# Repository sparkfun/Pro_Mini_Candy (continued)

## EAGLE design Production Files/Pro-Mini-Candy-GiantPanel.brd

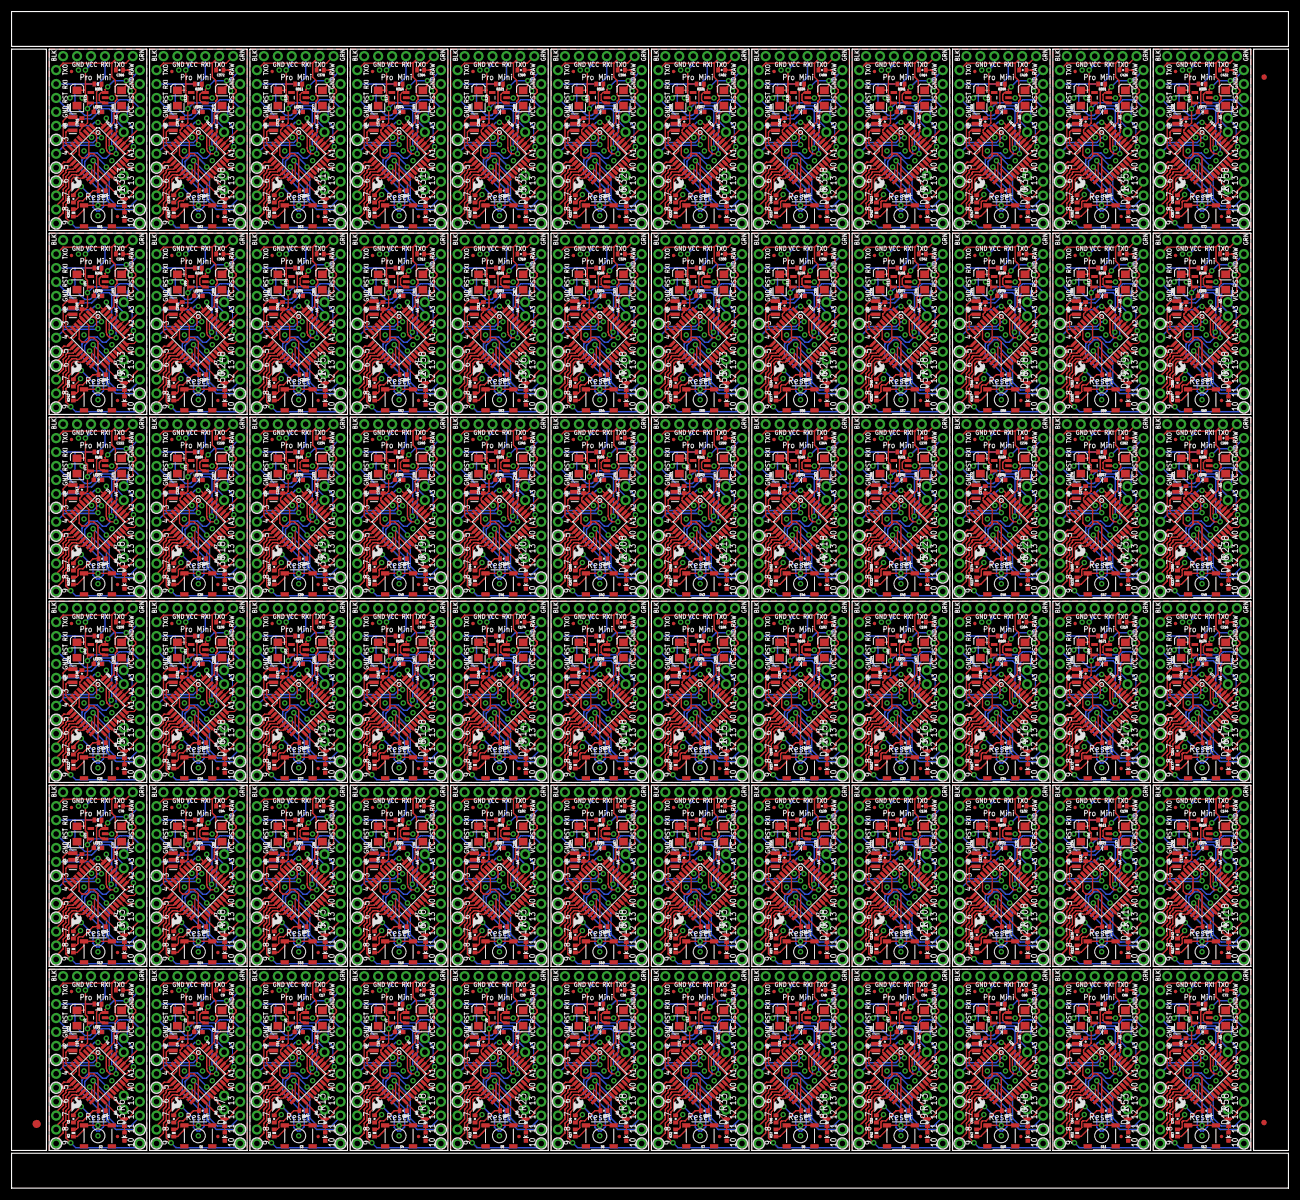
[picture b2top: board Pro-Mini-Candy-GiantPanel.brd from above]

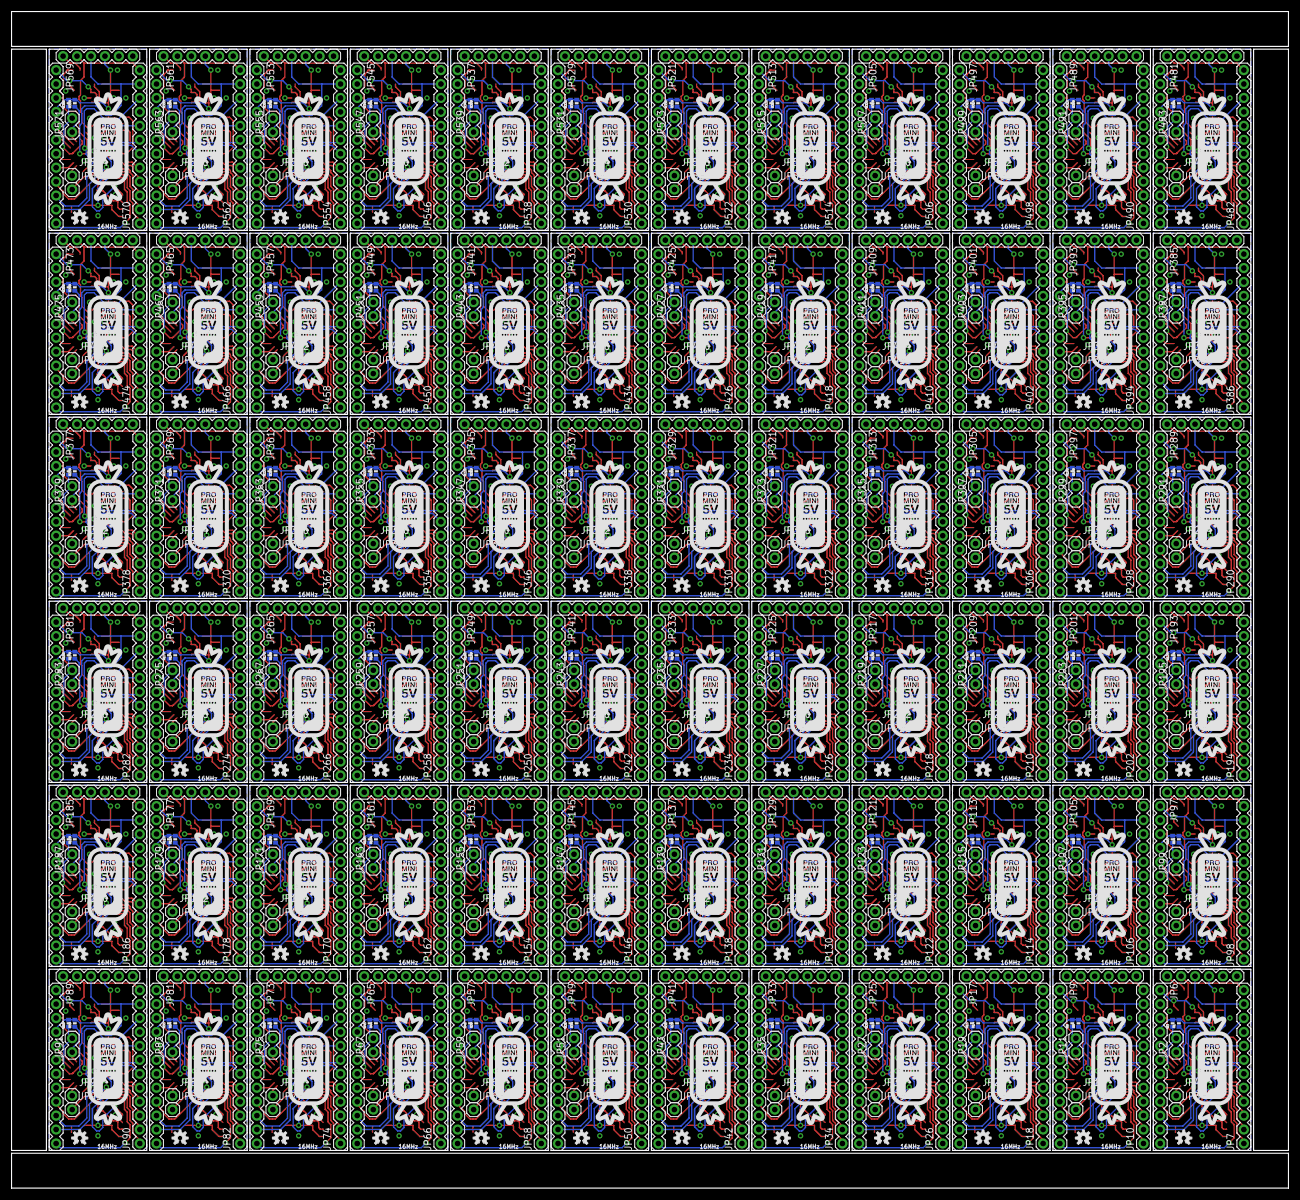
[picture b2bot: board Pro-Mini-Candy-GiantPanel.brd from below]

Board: 2 copper layers, 232.7 x 214.4 mm, 2019 parts (720 on the bottom side), 2304 nets.

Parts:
C1, C2, C3, C4, C6, C7, C9, C10, C11, C14, C15, C17, C18, C21, C22, C24, C25, C27, C28, C30, C31, C33, C34, C36, C37, C39, C40, C42, C43, C45, C46, C48, C49, C51, C52, C54, C55, C57, C58, C60, C61, C63, C64, C66, C67, C69, C70, C72, C73, C75, C76, C78, C79, C81, C82, C84, C85, C87, C88, C90, C91, C93, C94, C96, C97, C99, C100, C102, C103, C105, C106, C108, C109, C111, C112, C114, C115, C117, C118, C120, C121, C123, C124, C126, C127, C129, C130, C132, C133, C135, C136, C138, C139, C141, C142, C144, C145, C147, C148, C150, C151, C153, C154, C156, C157, C159, C160, C162, C163, C165, C166, C168, C169, C171, C172, C174, C175, C177, C178, C180, C181, C183, C184, C186, C187, C189, C190, C192, C193, C195, C196, C198, C199, C201, C202, C204, C205, C207, C208, C210, C211, C213, C214, C216, C217, C219, C220, C222, C223, C225, C226, C228, C229, C231, C232, C234, C235, C237, C238, C240, C241, C243, C244, C246, C247, C249, C250, C252, C253, C255, C256, C258, C259, C261, C262, C264, C265, C267, C268, C270, C271, C273, C274, C276, C277, C279, C280, C282, C283, C285, C286, C288, C289, C291, C292, C294, C295, C297, C298, C300, C301, C303, C304, C306, C307, C309, C310, C312, C313, C315, C316, C318, C319, C321, C322, C324, C325, C327, C328, C330, C331, C333, C334, C336, C337, C339, C340, C342, C343, C345, C346, C348, C349, C351, C352, C354, C355, C357, C358, C360, C361, C363, C364, C366, C367, C369, C370, C372, C373, C375, C376, C378, C379, C381, C382, C384, C385, C387, C388, C390, C391, C393, C394, C396, C397, C399, C400, C402, C403, C405, C406, C408, C409, C411, C412, C414, C415, C417, C418, C420, C421, C423, C424, C426, C427, C429, C430, C432: 0.1uF; 0402-CAP
C5, C8, C12, C13, C16, C19, C20, C23, C26, C29, C32, C35, C38, C41, C44, C47, C50, C53, C56, C59, C62, C65, C68, C71, C74, C77, C80, C83, C86, C89, C92, C95, C98, C101, C104, C107, C110, C113, C116, C119, C122, C125, C128, C131, C134, C137, C140, C143, C146, C149, C152, C155, C158, C161, C164, C167, C170, C173, C176, C179, C182, C185, C188, C191, C194, C197, C200, C203, C206, C209, C212, C215, C218, C221, C224, C227, C230, C233, C236, C239, C242, C245, C248, C251, C254, C257, C260, C263, C266, C269, C272, C275, C278, C281, C284, C287, C290, C293, C296, C299, C302, C305, C308, C311, C314, C317, C320, C323, C326, C329, C332, C335, C338, C341, C344, C347, C350, C353, C356, C359, C362, C365, C368, C371, C374, C377, C380, C383, C386, C389, C392, C395, C398, C401, C404, C407, C410, C413, C416, C419, C422, C425, C428, C431: 10uF; EIA3216
D1, D2, D3, D4, D5, D6, D7, D8, D9, D10, D11, D12, D13, D14, D15, D16, D17, D18, D19, D20, D21, D22, D23, D24, D25, D26, D27, D28, D29, D30, D31, D32, D33, D34, D35, D36, D37, D38, D39, D40, D41, D42, D43, D44, D45, D46, D47, D48, D49, D50, D51, D52, D53, D54, D55, D56, D57, D58, D59, D60, D61, D62, D63, D64, D65, D66, D67, D68, D69, D70, D71, D72: Green; LED-0603
E$1: FIDUCIAL-1.5X3
E$4, E$5: FIDUCIAL-1X2
JP1, JP12, JP20, JP28, JP36, JP44, JP52, JP60, JP68, JP76, JP84, JP92, JP100, JP108, JP116, JP124, JP132, JP140, JP148, JP156, JP164, JP172, JP180, JP188, JP196, JP204, JP212, JP220, JP228, JP236, JP244, JP252, JP260, JP268, JP276, JP284, JP292, JP300, JP308, JP316, JP324, JP332, JP340, JP348, JP356, JP364, JP372, JP380, JP388, JP396, JP404, JP412, JP420, JP428, JP436, JP444, JP452, JP460, JP468, JP476, JP484, JP492, JP500, JP508, JP516, JP524, JP532, JP540, JP548, JP556, JP564, JP572: FTDI Basic; 1X06
JP2, JP11, JP19, JP27, JP35, JP43, JP51, JP59, JP67, JP75, JP83, JP91, JP99, JP107, JP115, JP123, JP131, JP139, JP147, JP155, JP163, JP171, JP179, JP187, JP195, JP203, JP211, JP219, JP227, JP235, JP243, JP251, JP259, JP267, JP275, JP283, JP291, JP299, JP307, JP315, JP323, JP331, JP339, JP347, JP355, JP363, JP371, JP379, JP387, JP395, JP403, JP411, JP419, JP427, JP435, JP443, JP451, JP459, JP467, JP475, JP483, JP491, JP499, JP507, JP515, JP523, JP531, JP539, JP547, JP555, JP563, JP571: 1X02
JP3, JP4, JP13, JP14, JP21, JP22, JP29, JP30, JP37, JP38, JP45, JP46, JP53, JP54, JP61, JP62, JP69, JP70, JP77, JP78, JP85, JP86, JP93, JP94, JP101, JP102, JP109, JP110, JP117, JP118, JP125, JP126, JP133, JP134, JP141, JP142, JP149, JP150, JP157, JP158, JP165, JP166, JP173, JP174, JP181, JP182, JP189, JP190, JP197, JP198, JP205, JP206, JP213, JP214, JP221, JP222, JP229, JP230, JP237, JP238, JP245, JP246, JP253, JP254, JP261, JP262, JP269, JP270, JP277, JP278, JP285, JP286, JP293, JP294, JP301, JP302, JP309, JP310, JP317, JP318, JP325, JP326, JP333, JP334, JP341, JP342, JP349, JP350, JP357, JP358, JP365, JP366, JP373, JP374, JP381, JP382, JP389, JP390, JP397, JP398, JP405, JP406, JP413, JP414, JP421, JP422, JP429, JP430, JP437, JP438, JP445, JP446, JP453, JP454, JP461, JP462, JP469, JP470, JP477, JP478, JP485, JP486, JP493, JP494, JP501, JP502, JP509, JP510, JP517, JP518, JP525, JP526, JP533, JP534, JP541, JP542, JP549, JP550, JP557, JP558, JP565, JP566, JP573, JP574: 1X01
JP5, JP8, JP15, JP16, JP23, JP24, JP31, JP32, JP39, JP40, JP47, JP48, JP55, JP56, JP63, JP64, JP71, JP72, JP79, JP80, JP87, JP88, JP95, JP96, JP103, JP104, JP111, JP112, JP119, JP120, JP127, JP128, JP135, JP136, JP143, JP144, JP151, JP152, JP159, JP160, JP167, JP168, JP175, JP176, JP183, JP184, JP191, JP192, JP199, JP200, JP207, JP208, JP215, JP216, JP223, JP224, JP231, JP232, JP239, JP240, JP247, JP248, JP255, JP256, JP263, JP264, JP271, JP272, JP279, JP280, JP287, JP288, JP295, JP296, JP303, JP304, JP311, JP312, JP319, JP320, JP327, JP328, JP335, JP336, JP343, JP344, JP351, JP352, JP359, JP360, JP367, JP368, JP375, JP376, JP383, JP384, JP391, JP392, JP399, JP400, JP407, JP408, JP415, JP416, JP423, JP424, JP431, JP432, JP439, JP440, JP447, JP448, JP455, JP456, JP463, JP464, JP471, JP472, JP479, JP480, JP487, JP488, JP495, JP496, JP503, JP504, JP511, JP512, JP519, JP520, JP527, JP528, JP535, JP536, JP543, JP544, JP551, JP552, JP559, JP560, JP567, JP568, JP575, JP576: FIDUCIALUFIDUCIAL; MICRO-FIDUCIAL
JP6, JP7, JP9, JP10, JP17, JP18, JP25, JP26, JP33, JP34, JP41, JP42, JP49, JP50, JP57, JP58, JP65, JP66, JP73, JP74, JP81, JP82, JP89, JP90, JP97, JP98, JP105, JP106, JP113, JP114, JP121, JP122, JP129, JP130, JP137, JP138, JP145, JP146, JP153, JP154, JP161, JP162, JP169, JP170, JP177, JP178, JP185, JP186, JP193, JP194, JP201, JP202, JP209, JP210, JP217, JP218, JP225, JP226, JP233, JP234, JP241, JP242, JP249, JP250, JP257, JP258, JP265, JP266, JP273, JP274, JP281, JP282, JP289, JP290, JP297, JP298, JP305, JP306, JP313, JP314, JP321, JP322, JP329, JP330, JP337, JP338, JP345, JP346, JP353, JP354, JP361, JP362, JP369, JP370, JP377, JP378, JP385, JP386, JP393, JP394, JP401, JP402, JP409, JP410, JP417, JP418, JP425, JP426, JP433, JP434, JP441, JP442, JP449, JP450, JP457, JP458, JP465, JP466, JP473, JP474, JP481, JP482, JP489, JP490, JP497, JP498, JP505, JP506, JP513, JP514, JP521, JP522, JP529, JP530, JP537, JP538, JP545, JP546, JP553, JP554, JP561, JP562, JP569, JP570: 1X12
LED1, LED2, LED3, LED4, LED5, LED6, LED7, LED8, LED9, LED10, LED11, LED12, LED13, LED14, LED15, LED16, LED17, LED18, LED19, LED20, LED21, LED22, LED23, LED24, LED25, LED26, LED27, LED28, LED29, LED30, LED31, LED32, LED33, LED34, LED35, LED36, LED37, LED38, LED39, LED40, LED41, LED42, LED43, LED44, LED45, LED46, LED47, LED48, LED49, LED50, LED51, LED52, LED53, LED54, LED55, LED56, LED57, LED58, LED59, LED60, LED61, LED62, LED63, LED64, LED65, LED66, LED67, LED68, LED69, LED70, LED71, LED72: Red; LED-0603
Q1, Q2, Q3, Q4, Q5, Q6, Q7, Q8, Q9, Q10, Q11, Q12, Q13, Q14, Q15, Q16, Q17, Q18, Q19, Q20, Q21, Q22, Q23, Q24, Q25, Q26, Q27, Q28, Q29, Q30, Q31, Q32, Q33, Q34, Q35, Q36, Q37, Q38, Q39, Q40, Q41, Q42, Q43, Q44, Q45, Q46, Q47, Q48, Q49, Q50, Q51, Q52, Q53, Q54, Q55, Q56, Q57, Q58, Q59, Q60, Q61, Q62, Q63, Q64, Q65, Q66, Q67, Q68, Q69, Q70, Q71, Q72: 8/16/20MHz; RESONATOR-SMD
R1, R3, R8, R9, R14, R15, R19, R20, R24, R25, R29, R30, R34, R35, R39, R40, R44, R45, R49, R50, R54, R55, R59, R60, R64, R65, R69, R70, R74, R75, R79, R80, R84, R85, R89, R90, R94, R95, R99, R100, R104, R105, R109, R110, R114, R115, R119, R120, R124, R125, R129, R130, R134, R135, R139, R140, R144, R145, R149, R150, R154, R155, R159, R160, R164, R165, R169, R170, R174, R175, R179, R180, R184, R185, R189, R190, R194, R195, R199, R200, R204, R205, R209, R210, R214, R215, R219, R220, R224, R225, R229, R230, R234, R235, R239, R240, R244, R245, R249, R250, R254, R255, R259, R260, R264, R265, R269, R270, R274, R275, R279, R280, R284, R285, R289, R290, R294, R295, R299, R300, R304, R305, R309, R310, R314, R315, R319, R320, R324, R325, R329, R330, R334, R335, R339, R340, R344, R345, R349, R350, R354, R355, R359, R360: 0402-RES
R2, R4, R5, R10, R11, R12, R16, R17, R21, R22, R26, R27, R31, R32, R36, R37, R41, R42, R46, R47, R51, R52, R56, R57, R61, R62, R66, R67, R71, R72, R76, R77, R81, R82, R86, R87, R91, R92, R96, R97, R101, R102, R106, R107, R111, R112, R116, R117, R121, R122, R126, R127, R131, R132, R136, R137, R141, R142, R146, R147, R151, R152, R156, R157, R161, R162, R166, R167, R171, R172, R176, R177, R181, R182, R186, R187, R191, R192, R196, R197, R201, R202, R206, R207, R211, R212, R216, R217, R221, R222, R226, R227, R231, R232, R236, R237, R241, R242, R246, R247, R251, R252, R256, R257, R261, R262, R266, R267, R271, R272, R276, R277, R281, R282, R286, R287, R291, R292, R296, R297, R301, R302, R306, R307, R311, R312, R316, R317, R321, R322, R326, R327, R331, R332, R336, R337, R341, R342, R346, R347, R351, R352, R356, R357: 10K; 0402-RES
R6, R7, R13, R18, R23, R28, R33, R38, R43, R48, R53, R58, R63, R68, R73, R78, R83, R88, R93, R98, R103, R108, R113, R118, R123, R128, R133, R138, R143, R148, R153, R158, R163, R168, R173, R178, R183, R188, R193, R198, R203, R208, R213, R218, R223, R228, R233, R238, R243, R248, R253, R258, R263, R268, R273, R278, R283, R288, R293, R298, R303, R308, R313, R318, R323, R328, R333, R338, R343, R348, R353, R358: 330; 0402-RES
S1, S2, S3, S4, S5, S6, S7, S8, S9, S10, S11, S12, S13, S14, S15, S16, S17, S18, S19, S20, S21, S22, S23, S24, S25, S26, S27, S28, S29, S30, S31, S32, S33, S34, S35, S36, S37, S38, S39, S40, S41, S42, S43, S44, S45, S46, S47, S48, S49, S50, S51, S52, S53, S54, S55, S56, S57, S58, S59, S60, S61, S62, S63, S64, S65, S66, S67, S68, S69, S70, S71, S72: Reset; TACTILE_SWITCH_SMD
U1, U4, U6, U8, U10, U12, U14, U16, U18, U20, U22, U24, U26, U28, U30, U32, U34, U36, U38, U40, U42, U44, U46, U48, U50, U52, U54, U56, U58, U60, U62, U64, U66, U68, U70, U72, U74, U76, U78, U80, U82, U84, U86, U88, U90, U92, U94, U96, U98, U100, U102, U104, U106, U108, U110, U112, U114, U116, U118, U120, U122, U124, U126, U128, U130, U132, U134, U136, U138, U140, U142, U144: ATMEGA328; TQFP32-08
U2, U3, U5, U7, U9, U11, U13, U15, U17, U19, U21, U23, U25, U27, U29, U31, U33, U35, U37, U39, U41, U43, U45, U47, U49, U51, U53, U55, U57, U59, U61, U63, U65, U67, U69, U71, U73, U75, U77, U79, U81, U83, U85, U87, U89, U91, U93, U95, U97, U99, U101, U103, U105, U107, U109, U111, U113, U115, U117, U119, U121, U123, U125, U127, U129, U131, U133, U135, U137, U139, U141, U143: MIC5205; SOT23-5
U$1, U$4, U$7, U$10, U$13, U$16, U$19, U$22, U$25, U$28, U$31, U$34, U$37, U$40, U$43, U$46, U$49, U$52, U$55, U$58, U$61, U$64, U$67, U$70, U$73, U$76, U$79, U$82, U$85, U$88, U$91, U$94, U$97, U$100, U$103, U$106, U$109, U$112, U$115, U$118, U$121, U$124, U$127, U$130, U$133, U$136, U$139, U$142, U$145, U$148, U$151, U$154, U$157, U$160, U$163, U$166, U$169, U$172, U$175, U$178, U$181, U$184, U$187, U$190, U$193, U$196, U$199, U$202, U$205, U$208, U$211, U$214: LOGO-SFESK; SFE-LOGO-FLAME
U$2, U$6, U$9, U$12, U$15, U$18, U$21, U$24, U$27, U$30, U$33, U$36, U$39, U$42, U$45, U$48, U$51, U$54, U$57, U$60, U$63, U$66, U$69, U$72, U$75, U$78, U$81, U$84, U$87, U$90, U$93, U$96, U$99, U$102, U$105, U$108, U$111, U$114, U$117, U$120, U$123, U$126, U$129, U$132, U$135, U$138, U$141, U$144, U$147, U$150, U$153, U$156, U$159, U$162, U$165, U$168, U$171, U$174, U$177, U$180, U$183, U$186, U$189, U$192, U$195, U$198, U$201, U$204, U$207, U$210, U$213, U$216: PRO_MINI_CANDY
U$3, U$5, U$8, U$11, U$14, U$17, U$20, U$23, U$26, U$29, U$32, U$35, U$38, U$41, U$44, U$47, U$50, U$53, U$56, U$59, U$62, U$65, U$68, U$71, U$74, U$77, U$80, U$83, U$86, U$89, U$92, U$95, U$98, U$101, U$104, U$107, U$110, U$113, U$116, U$119, U$122, U$125, U$128, U$131, U$134, U$137, U$140, U$143, U$146, U$149, U$152, U$155, U$158, U$161, U$164, U$167, U$170, U$173, U$176, U$179, U$182, U$185, U$188, U$191, U$194, U$197, U$200, U$203, U$206, U$209, U$212, U$215: OSHW-LOGOS; OSHW-LOGO-S

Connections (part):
A0: JP6.8, U1.23
A1: JP6.7, U1.24
A2: JP6.6, U1.25
A3: JP6.5, U1.26
A4: JP2.1, R1.1, U1.27
A5: JP2.2, R3.1, U1.28
A6: JP3.1, U1.19
A7: JP4.1, U1.22
A8: JP11.2, R9.1, U4.28
A9: JP11.1, R8.1, U4.27
A10: JP9.5, U4.26
A11: JP9.6, U4.25
A12: JP9.7, U4.24
A13: JP9.8, U4.23
A14: JP13.1, U4.19
A15: JP14.1, U4.22
A16: JP19.2, R15.1, U6.28
A17: JP19.1, R14.1, U6.27
A18: JP17.5, U6.26
A19: JP17.6, U6.25
A20: JP17.7, U6.24
A21: JP17.8, U6.23
A22: JP21.1, U6.19
A23: JP22.1, U6.22
A24: JP27.2, R20.1, U8.28
A25: JP27.1, R19.1, U8.27
A26: JP25.5, U8.26
A27: JP25.6, U8.25
A28: JP25.7, U8.24
A29: JP25.8, U8.23
A30: JP29.1, U8.19
A31: JP30.1, U8.22
A32: JP35.2, R25.1, U10.28
A33: JP35.1, R24.1, U10.27
A34: JP33.5, U10.26
A35: JP33.6, U10.25
A36: JP33.7, U10.24
A37: JP33.8, U10.23
A38: JP37.1, U10.19
A39: JP38.1, U10.22
A40: JP43.2, R30.1, U12.28
A41: JP43.1, R29.1, U12.27
A42: JP41.5, U12.26
A43: JP41.6, U12.25
A44: JP41.7, U12.24
A45: JP41.8, U12.23
A46: JP45.1, U12.19
A47: JP46.1, U12.22
A48: JP51.2, R35.1, U14.28
A49: JP51.1, R34.1, U14.27
A50: JP49.5, U14.26
A51: JP49.6, U14.25
A52: JP49.7, U14.24
A53: JP49.8, U14.23
A54: JP53.1, U14.19
A55: JP54.1, U14.22
A56: JP59.2, R40.1, U16.28
A57: JP59.1, R39.1, U16.27
A58: JP57.5, U16.26
A59: JP57.6, U16.25
A60: JP57.7, U16.24
A61: JP57.8, U16.23
A62: JP61.1, U16.19
A63: JP62.1, U16.22
A64: JP67.2, R45.1, U18.28
A65: JP67.1, R44.1, U18.27
A66: JP65.5, U18.26
A67: JP65.6, U18.25
A68: JP65.7, U18.24
A69: JP65.8, U18.23
A70: JP69.1, U18.19
A71: JP70.1, U18.22
A72: JP75.2, R50.1, U20.28
A73: JP75.1, R49.1, U20.27
A74: JP73.5, U20.26
A75: JP73.6, U20.25
A76: JP73.7, U20.24
A77: JP73.8, U20.23
A78: JP77.1, U20.19
A79: JP78.1, U20.22
A80: JP83.2, R55.1, U22.28
A81: JP83.1, R54.1, U22.27
A82: JP81.5, U22.26
A83: JP81.6, U22.25
A84: JP81.7, U22.24
A85: JP81.8, U22.23
A86: JP85.1, U22.19
A87: JP86.1, U22.22
A88: JP91.2, R60.1, U24.28
A89: JP91.1, R59.1, U24.27
A90: JP89.5, U24.26
A91: JP89.6, U24.25
A92: JP89.7, U24.24
A93: JP89.8, U24.23
A94: JP93.1, U24.19
A95: JP94.1, U24.22
A96: JP99.2, R65.1, U26.28
A97: JP99.1, R64.1, U26.27
A98: JP97.5, U26.26
A99: JP97.6, U26.25
A100: JP97.7, U26.24
A101: JP97.8, U26.23
A102: JP101.1, U26.19
A103: JP102.1, U26.22
A104: JP107.2, R70.1, U28.28
A105: JP107.1, R69.1, U28.27
A106: JP105.5, U28.26
A107: JP105.6, U28.25
A108: JP105.7, U28.24
A109: JP105.8, U28.23
A110: JP109.1, U28.19
A111: JP110.1, U28.22
A112: JP115.2, R75.1, U30.28
A113: JP115.1, R74.1, U30.27
A114: JP113.5, U30.26
A115: JP113.6, U30.25
A116: JP113.7, U30.24
A117: JP113.8, U30.23
A118: JP117.1, U30.19
A119: JP118.1, U30.22
A120: JP123.2, R80.1, U32.28
A121: JP123.1, R79.1, U32.27
A122: JP121.5, U32.26
A123: JP121.6, U32.25
A124: JP121.7, U32.24
A125: JP121.8, U32.23
A126: JP125.1, U32.19
A127: JP126.1, U32.22
A128: JP131.2, R85.1, U34.28
A129: JP131.1, R84.1, U34.27
A130: JP129.5, U34.26
A131: JP129.6, U34.25
A132: JP129.7, U34.24
A133: JP129.8, U34.23
A134: JP133.1, U34.19
A135: JP134.1, U34.22
A136: JP139.2, R90.1, U36.28
A137: JP139.1, R89.1, U36.27
A138: JP137.5, U36.26
A139: JP137.6, U36.25
A140: JP137.7, U36.24
A141: JP137.8, U36.23
A142: JP141.1, U36.19
A143: JP142.1, U36.22
A144: JP147.2, R95.1, U38.28
A145: JP147.1, R94.1, U38.27
A146: JP145.5, U38.26
A147: JP145.6, U38.25
A148: JP145.7, U38.24
A149: JP145.8, U38.23
A150: JP149.1, U38.19
A151: JP150.1, U38.22
A152: JP155.2, R100.1, U40.28
A153: JP155.1, R99.1, U40.27
A154: JP153.5, U40.26
A155: JP153.6, U40.25
A156: JP153.7, U40.24
A157: JP153.8, U40.23
A158: JP157.1, U40.19
A159: JP158.1, U40.22
A160: JP163.2, R105.1, U42.28
A161: JP163.1, R104.1, U42.27
A162: JP161.5, U42.26
A163: JP161.6, U42.25
A164: JP161.7, U42.24
A165: JP161.8, U42.23
A166: JP165.1, U42.19
A167: JP166.1, U42.22
A168: JP171.2, R110.1, U44.28
A169: JP171.1, R109.1, U44.27
A170: JP169.5, U44.26
A171: JP169.6, U44.25
A172: JP169.7, U44.24
A173: JP169.8, U44.23
A174: JP173.1, U44.19
A175: JP174.1, U44.22
A176: JP179.2, R115.1, U46.28
A177: JP179.1, R114.1, U46.27
A178: JP177.5, U46.26
A179: JP177.6, U46.25
A180: JP177.7, U46.24
A181: JP177.8, U46.23
A182: JP181.1, U46.19
A183: JP182.1, U46.22
A184: JP187.2, R120.1, U48.28
A185: JP187.1, R119.1, U48.27
A186: JP185.5, U48.26
A187: JP185.6, U48.25
A188: JP185.7, U48.24
A189: JP185.8, U48.23
A190: JP189.1, U48.19
A191: JP190.1, U48.22
A192: JP195.2, R125.1, U50.28
A193: JP195.1, R124.1, U50.27
A194: JP193.5, U50.26
A195: JP193.6, U50.25
A196: JP193.7, U50.24
A197: JP193.8, U50.23
A198: JP197.1, U50.19
A199: JP198.1, U50.22
A200: JP203.2, R130.1, U52.28
A201: JP203.1, R129.1, U52.27
A202: JP201.5, U52.26
A203: JP201.6, U52.25
A204: JP201.7, U52.24
A205: JP201.8, U52.23
A206: JP205.1, U52.19
A207: JP206.1, U52.22
A208: JP211.2, R135.1, U54.28
A209: JP211.1, R134.1, U54.27
A210: JP209.5, U54.26
A211: JP209.6, U54.25
A212: JP209.7, U54.24
A213: JP209.8, U54.23
A214: JP213.1, U54.19
A215: JP214.1, U54.22
A216: JP219.2, R140.1, U56.28
A217: JP219.1, R139.1, U56.27
A218: JP217.5, U56.26
A219: JP217.6, U56.25
A220: JP217.7, U56.24
A221: JP217.8, U56.23
A222: JP221.1, U56.19
A223: JP222.1, U56.22
A224: JP227.2, R145.1, U58.28
A225: JP227.1, R144.1, U58.27
A226: JP225.5, U58.26
A227: JP225.6, U58.25
A228: JP225.7, U58.24
A229: JP225.8, U58.23
A230: JP229.1, U58.19
A231: JP230.1, U58.22
A232: JP235.2, R150.1, U60.28
A233: JP235.1, R149.1, U60.27
A234: JP233.5, U60.26
A235: JP233.6, U60.25
A236: JP233.7, U60.24
A237: JP233.8, U60.23
A238: JP237.1, U60.19
A239: JP238.1, U60.22
A240: JP243.2, R155.1, U62.28
A241: JP243.1, R154.1, U62.27
A242: JP241.5, U62.26
A243: JP241.6, U62.25
A244: JP241.7, U62.24
A245: JP241.8, U62.23
A246: JP245.1, U62.19
A247: JP246.1, U62.22
A248: JP251.2, R160.1, U64.28
A249: JP251.1, R159.1, U64.27
A250: JP249.5, U64.26
A251: JP249.6, U64.25
A252: JP249.7, U64.24
A253: JP249.8, U64.23
A254: JP253.1, U64.19
A255: JP254.1, U64.22
A256: JP259.2, R165.1, U66.28
A257: JP259.1, R164.1, U66.27
A258: JP257.5, U66.26
A259: JP257.6, U66.25
A260: JP257.7, U66.24
A261: JP257.8, U66.23
A262: JP261.1, U66.19
A263: JP262.1, U66.22
A264: JP267.2, R170.1, U68.28
A265: JP267.1, R169.1, U68.27
A266: JP265.5, U68.26
A267: JP265.6, U68.25
A268: JP265.7, U68.24
A269: JP265.8, U68.23
A270: JP269.1, U68.19
A271: JP270.1, U68.22
A272: JP275.2, R175.1, U70.28
A273: JP275.1, R174.1, U70.27
A274: JP273.5, U70.26
A275: JP273.6, U70.25
A276: JP273.7, U70.24
A277: JP273.8, U70.23
A278: JP277.1, U70.19
A279: JP278.1, U70.22
A280: JP283.2, R180.1, U72.28
A281: JP283.1, R179.1, U72.27
A282: JP281.5, U72.26
A283: JP281.6, U72.25
A284: JP281.7, U72.24
A285: JP281.8, U72.23
A286: JP285.1, U72.19
A287: JP286.1, U72.22
A288: JP291.2, R185.1, U74.28
A289: JP291.1, R184.1, U74.27
A290: JP289.5, U74.26
A291: JP289.6, U74.25
A292: JP289.7, U74.24
A293: JP289.8, U74.23
A294: JP293.1, U74.19
A295: JP294.1, U74.22
A296: JP299.2, R190.1, U76.28
A297: JP299.1, R189.1, U76.27
A298: JP297.5, U76.26
A299: JP297.6, U76.25
A300: JP297.7, U76.24
A301: JP297.8, U76.23
A302: JP301.1, U76.19
A303: JP302.1, U76.22
A304: JP307.2, R195.1, U78.28
A305: JP307.1, R194.1, U78.27
A306: JP305.5, U78.26
A307: JP305.6, U78.25
A308: JP305.7, U78.24
A309: JP305.8, U78.23
A310: JP309.1, U78.19
A311: JP310.1, U78.22
A312: JP315.2, R200.1, U80.28
A313: JP315.1, R199.1, U80.27
A314: JP313.5, U80.26
A315: JP313.6, U80.25
A316: JP313.7, U80.24
A317: JP313.8, U80.23
A318: JP317.1, U80.19
A319: JP318.1, U80.22
A320: JP323.2, R205.1, U82.28
A321: JP323.1, R204.1, U82.27
A322: JP321.5, U82.26
A323: JP321.6, U82.25
A324: JP321.7, U82.24
A325: JP321.8, U82.23
A326: JP325.1, U82.19
A327: JP326.1, U82.22
A328: JP331.2, R210.1, U84.28
A329: JP331.1, R209.1, U84.27
A330: JP329.5, U84.26
A331: JP329.6, U84.25
A332: JP329.7, U84.24
A333: JP329.8, U84.23
A334: JP333.1, U84.19
A335: JP334.1, U84.22
A336: JP339.2, R215.1, U86.28
A337: JP339.1, R214.1, U86.27
A338: JP337.5, U86.26
A339: JP337.6, U86.25
A340: JP337.7, U86.24
A341: JP337.8, U86.23
A342: JP341.1, U86.19
A343: JP342.1, U86.22
A344: JP347.2, R220.1, U88.28
A345: JP347.1, R219.1, U88.27
A346: JP345.5, U88.26
A347: JP345.6, U88.25
A348: JP345.7, U88.24
A349: JP345.8, U88.23
A350: JP349.1, U88.19
A351: JP350.1, U88.22
A352: JP355.2, R225.1, U90.28
A353: JP355.1, R224.1, U90.27
A354: JP353.5, U90.26
A355: JP353.6, U90.25
A356: JP353.7, U90.24
A357: JP353.8, U90.23
A358: JP357.1, U90.19
A359: JP358.1, U90.22
A360: JP363.2, R230.1, U92.28
A361: JP363.1, R229.1, U92.27
A362: JP361.5, U92.26
A363: JP361.6, U92.25
A364: JP361.7, U92.24
A365: JP361.8, U92.23
A366: JP365.1, U92.19
A367: JP366.1, U92.22
A368: JP371.2, R235.1, U94.28
A369: JP371.1, R234.1, U94.27
A370: JP369.5, U94.26
A371: JP369.6, U94.25
A372: JP369.7, U94.24
A373: JP369.8, U94.23
A374: JP373.1, U94.19
A375: JP374.1, U94.22
A376: JP379.2, R240.1, U96.28
A377: JP379.1, R239.1, U96.27
A378: JP377.5, U96.26
A379: JP377.6, U96.25
A380: JP377.7, U96.24
A381: JP377.8, U96.23
A382: JP381.1, U96.19
A383: JP382.1, U96.22
A384: JP387.2, R245.1, U98.28
A385: JP387.1, R244.1, U98.27
A386: JP385.5, U98.26
A387: JP385.6, U98.25
A388: JP385.7, U98.24
A389: JP385.8, U98.23
A390: JP389.1, U98.19
A391: JP390.1, U98.22
A392: JP395.2, R250.1, U100.28
A393: JP395.1, R249.1, U100.27
A394: JP393.5, U100.26
A395: JP393.6, U100.25
A396: JP393.7, U100.24
A397: JP393.8, U100.23
A398: JP397.1, U100.19
A399: JP398.1, U100.22
A400: JP403.2, R255.1, U102.28
A401: JP403.1, R254.1, U102.27
A402: JP401.5, U102.26
A403: JP401.6, U102.25
A404: JP401.7, U102.24
A405: JP401.8, U102.23
A406: JP405.1, U102.19
A407: JP406.1, U102.22
A408: JP411.2, R260.1, U104.28
A409: JP411.1, R259.1, U104.27
A410: JP409.5, U104.26
A411: JP409.6, U104.25
A412: JP409.7, U104.24
A413: JP409.8, U104.23
A414: JP413.1, U104.19
A415: JP414.1, U104.22
A416: JP419.2, R265.1, U106.28
A417: JP419.1, R264.1, U106.27
A418: JP417.5, U106.26
A419: JP417.6, U106.25
A420: JP417.7, U106.24
A421: JP417.8, U106.23
A422: JP421.1, U106.19
A423: JP422.1, U106.22
A424: JP427.2, R270.1, U108.28
A425: JP427.1, R269.1, U108.27
A426: JP425.5, U108.26
A427: JP425.6, U108.25
A428: JP425.7, U108.24
A429: JP425.8, U108.23
A430: JP429.1, U108.19
A431: JP430.1, U108.22
A432: JP435.2, R275.1, U110.28
A433: JP435.1, R274.1, U110.27
A434: JP433.5, U110.26
A435: JP433.6, U110.25
A436: JP433.7, U110.24
A437: JP433.8, U110.23
A438: JP437.1, U110.19
A439: JP438.1, U110.22
A440: JP443.2, R280.1, U112.28
A441: JP443.1, R279.1, U112.27
A442: JP441.5, U112.26
A443: JP441.6, U112.25
A444: JP441.7, U112.24
A445: JP441.8, U112.23
A446: JP445.1, U112.19
A447: JP446.1, U112.22
A448: JP451.2, R285.1, U114.28
A449: JP451.1, R284.1, U114.27
A450: JP449.5, U114.26
A451: JP449.6, U114.25
A452: JP449.7, U114.24
A453: JP449.8, U114.23
A454: JP453.1, U114.19
A455: JP454.1, U114.22
A456: JP459.2, R290.1, U116.28
A457: JP459.1, R289.1, U116.27
A458: JP457.5, U116.26
A459: JP457.6, U116.25
A460: JP457.7, U116.24
A461: JP457.8, U116.23
A462: JP461.1, U116.19
A463: JP462.1, U116.22
A464: JP467.2, R295.1, U118.28
A465: JP467.1, R294.1, U118.27
A466: JP465.5, U118.26
A467: JP465.6, U118.25
A468: JP465.7, U118.24
A469: JP465.8, U118.23
A470: JP469.1, U118.19
A471: JP470.1, U118.22
A472: JP475.2, R300.1, U120.28
A473: JP475.1, R299.1, U120.27
A474: JP473.5, U120.26
A475: JP473.6, U120.25
A476: JP473.7, U120.24
A477: JP473.8, U120.23
A478: JP477.1, U120.19
A479: JP478.1, U120.22
A480: JP483.2, R305.1, U122.28
A481: JP483.1, R304.1, U122.27
A482: JP481.5, U122.26
A483: JP481.6, U122.25
A484: JP481.7, U122.24
A485: JP481.8, U122.23
A486: JP485.1, U122.19
A487: JP486.1, U122.22
A488: JP491.2, R310.1, U124.28
A489: JP491.1, R309.1, U124.27
A490: JP489.5, U124.26
A491: JP489.6, U124.25
A492: JP489.7, U124.24
A493: JP489.8, U124.23
A494: JP493.1, U124.19
A495: JP494.1, U124.22
A496: JP499.2, R315.1, U126.28
A497: JP499.1, R314.1, U126.27
A498: JP497.5, U126.26
A499: JP497.6, U126.25
A500: JP497.7, U126.24
A501: JP497.8, U126.23
A502: JP501.1, U126.19
A503: JP502.1, U126.22
A504: JP507.2, R320.1, U128.28
A505: JP507.1, R319.1, U128.27
A506: JP505.5, U128.26
A507: JP505.6, U128.25
A508: JP505.7, U128.24
A509: JP505.8, U128.23
A510: JP509.1, U128.19
A511: JP510.1, U128.22
A512: JP515.2, R325.1, U130.28
A513: JP515.1, R324.1, U130.27
A514: JP513.5, U130.26
A515: JP513.6, U130.25
A516: JP513.7, U130.24
A517: JP513.8, U130.23
A518: JP517.1, U130.19
A519: JP518.1, U130.22
A520: JP523.2, R330.1, U132.28
A521: JP523.1, R329.1, U132.27
A522: JP521.5, U132.26
A523: JP521.6, U132.25
A524: JP521.7, U132.24
A525: JP521.8, U132.23
A526: JP525.1, U132.19
A527: JP526.1, U132.22
A528: JP531.2, R335.1, U134.28
A529: JP531.1, R334.1, U134.27
A530: JP529.5, U134.26
A531: JP529.6, U134.25
A532: JP529.7, U134.24
A533: JP529.8, U134.23
A534: JP533.1, U134.19
A535: JP534.1, U134.22
A536: JP539.2, R340.1, U136.28
A537: JP539.1, R339.1, U136.27
A538: JP537.5, U136.26
A539: JP537.6, U136.25
A540: JP537.7, U136.24
A541: JP537.8, U136.23
A542: JP541.1, U136.19
A543: JP542.1, U136.22
A544: JP547.2, R345.1, U138.28
A545: JP547.1, R344.1, U138.27
A546: JP545.5, U138.26
A547: JP545.6, U138.25
A548: JP545.7, U138.24
A549: JP545.8, U138.23
A550: JP549.1, U138.19
A551: JP550.1, U138.22
A552: JP555.2, R350.1, U140.28
A553: JP555.1, R349.1, U140.27
A554: JP553.5, U140.26
A555: JP553.6, U140.25
A556: JP553.7, U140.24
A557: JP553.8, U140.23
A558: JP557.1, U140.19
A559: JP558.1, U140.22
A560: JP563.2, R355.1, U142.28
A561: JP563.1, R354.1, U142.27
A562: JP561.5, U142.26
A563: JP561.6, U142.25
A564: JP561.7, U142.24
A565: JP561.8, U142.23
A566: JP565.1, U142.19
A567: JP566.1, U142.22
A568: JP571.2, R360.1, U144.28
A569: JP571.1, R359.1, U144.27
A570: JP569.5, U144.26
A571: JP569.6, U144.25
A572: JP569.7, U144.24
A573: JP569.8, U144.23
A574: JP573.1, U144.19
A575: JP574.1, U144.22
AREF: C1.2, U1.20
AREF1: C7.2, U4.20
AREF2: C15.2, U6.20
AREF3: C22.2, U8.20
AREF4: C28.2, U10.20
AREF5: C34.2, U12.20
AREF6: C40.2, U14.20
AREF7: C46.2, U16.20
AREF8: C52.2, U18.20
AREF9: C58.2, U20.20
AREF10: C64.2, U22.20
AREF11: C70.2, U24.20
AREF12: C76.2, U26.20
AREF13: C82.2, U28.20
AREF14: C88.2, U30.20
AREF15: C94.2, U32.20
AREF16: C100.2, U34.20
AREF17: C106.2, U36.20
AREF18: C112.2, U38.20
AREF19: C118.2, U40.20
AREF20: C124.2, U42.20
AREF21: C130.2, U44.20
AREF22: C136.2, U46.20
AREF23: C142.2, U48.20
AREF24: C148.2, U50.20
AREF25: C154.2, U52.20
AREF26: C160.2, U54.20
AREF27: C166.2, U56.20
AREF28: C172.2, U58.20
AREF29: C178.2, U60.20
AREF30: C184.2, U62.20
AREF31: C190.2, U64.20
AREF32: C196.2, U66.20
AREF33: C202.2, U68.20
AREF34: C208.2, U70.20
AREF35: C214.2, U72.20
AREF36: C220.2, U74.20
AREF37: C226.2, U76.20
AREF38: C232.2, U78.20
AREF39: C238.2, U80.20
AREF40: C244.2, U82.20
AREF41: C250.2, U84.20
AREF42: C256.2, U86.20
AREF43: C262.2, U88.20
AREF44: C268.2, U90.20
AREF45: C274.2, U92.20
AREF46: C280.2, U94.20
AREF47: C286.2, U96.20
AREF48: C292.2, U98.20
AREF49: C298.2, U100.20
AREF50: C304.2, U102.20
AREF51: C310.2, U104.20
AREF52: C316.2, U106.20
AREF53: C322.2, U108.20
AREF54: C328.2, U110.20
AREF55: C334.2, U112.20
AREF56: C340.2, U114.20
AREF57: C346.2, U116.20
AREF58: C352.2, U118.20
AREF59: C358.2, U120.20
AREF60: C364.2, U122.20
AREF61: C370.2, U124.20
AREF62: C376.2, U126.20
AREF63: C382.2, U128.20
AREF64: C388.2, U130.20
AREF65: C394.2, U132.20
AREF66: C400.2, U134.20
AREF67: C406.2, U136.20
AREF68: C412.2, U138.20
AREF69: C418.2, U140.20
AREF70: C424.2, U142.20
AREF71: C430.2, U144.20
D1: JP10.1, U4.13
D2: JP7.8, U1.32
D3: JP7.7, U1.1
D4: JP7.6, U1.2
D5: JP7.5, U1.9
D6: JP7.4, U1.10
D7: JP7.3, U1.11
D8: JP7.2, U1.12
D9: JP7.1, U1.13
D10: JP6.12, U1.14
D11: JP10.2, U4.12
D12: JP10.8, U4.32
D13: JP10.7, U4.1
D14: JP10.6, U4.2
D15: JP10.5, U4.9
D16: JP10.4, U4.10
D17: JP10.3, U4.11
D18: JP9.12, U4.14
D19: JP18.1, U6.13
D20: JP18.2, U6.12
D21: JP18.8, U6.32
D22: JP18.7, U6.1
D23: JP18.6, U6.2
D24: JP18.5, U6.9
D25: JP18.4, U6.10
D26: JP18.3, U6.11
D27: JP17.12, U6.14
D28: JP26.1, U8.13
D29: JP26.2, U8.12
D30: JP26.8, U8.32
D31: JP26.7, U8.1
D32: JP26.6, U8.2
D33: JP26.5, U8.9
D34: JP26.4, U8.10
D35: JP26.3, U8.11
D36: JP25.12, U8.14
D37: JP34.1, U10.13
D38: JP34.2, U10.12
D39: JP34.8, U10.32
D40: JP34.7, U10.1
D41: JP34.6, U10.2
D42: JP34.5, U10.9
D43: JP34.4, U10.10
D44: JP34.3, U10.11
D45: JP33.12, U10.14
D46: JP42.1, U12.13
D47: JP42.2, U12.12
D48: JP42.8, U12.32
D49: JP42.7, U12.1
D50: JP42.6, U12.2
D51: JP42.5, U12.9
D52: JP42.4, U12.10
D53: JP42.3, U12.11
D54: JP41.12, U12.14
D55: JP50.1, U14.13
D56: JP50.2, U14.12
D57: JP50.8, U14.32
D58: JP50.7, U14.1
D59: JP50.6, U14.2
D60: JP50.5, U14.9
D61: JP50.4, U14.10
D62: JP50.3, U14.11
D63: JP49.12, U14.14
D64: JP58.1, U16.13
D65: JP58.2, U16.12
D66: JP58.8, U16.32
D67: JP58.7, U16.1
D68: JP58.6, U16.2
D69: JP58.5, U16.9
D70: JP58.4, U16.10
D71: JP58.3, U16.11
D72: JP57.12, U16.14
D73: JP66.1, U18.13
D74: JP66.2, U18.12
D75: JP66.8, U18.32
D76: JP66.7, U18.1
D77: JP66.6, U18.2
D78: JP66.5, U18.9
D79: JP66.4, U18.10
D80: JP66.3, U18.11
D81: JP65.12, U18.14
D82: JP74.1, U20.13
D83: JP74.2, U20.12
D84: JP74.8, U20.32
D85: JP74.7, U20.1
D86: JP74.6, U20.2
D87: JP74.5, U20.9
D88: JP74.4, U20.10
D89: JP74.3, U20.11
D90: JP73.12, U20.14
D91: JP82.1, U22.13
D92: JP82.2, U22.12
D93: JP82.8, U22.32
D94: JP82.7, U22.1
D95: JP82.6, U22.2
D96: JP82.5, U22.9
D97: JP82.4, U22.10
D98: JP82.3, U22.11
D99: JP81.12, U22.14
D100: JP90.1, U24.13
D101: JP90.2, U24.12
D102: JP90.8, U24.32
D103: JP90.7, U24.1
D104: JP90.6, U24.2
D105: JP90.5, U24.9
D106: JP90.4, U24.10
D107: JP90.3, U24.11
D108: JP89.12, U24.14
D109: JP98.1, U26.13
D110: JP98.2, U26.12
D111: JP98.8, U26.32
D112: JP98.7, U26.1
D113: JP98.6, U26.2
D114: JP98.5, U26.9
D115: JP98.4, U26.10
D116: JP98.3, U26.11
D117: JP97.12, U26.14
D118: JP106.1, U28.13
D119: JP106.2, U28.12
D120: JP106.8, U28.32
D121: JP106.7, U28.1
D122: JP106.6, U28.2
D123: JP106.5, U28.9
D124: JP106.4, U28.10
D125: JP106.3, U28.11
D126: JP105.12, U28.14
D127: JP114.1, U30.13
D128: JP114.2, U30.12
D129: JP114.8, U30.32
D130: JP114.7, U30.1
D131: JP114.6, U30.2
D132: JP114.5, U30.9
D133: JP114.4, U30.10
D134: JP114.3, U30.11
D135: JP113.12, U30.14
D136: JP122.1, U32.13
D137: JP122.2, U32.12
D138: JP122.8, U32.32
D139: JP122.7, U32.1
D140: JP122.6, U32.2
D141: JP122.5, U32.9
D142: JP122.4, U32.10
D143: JP122.3, U32.11
D144: JP121.12, U32.14
D145: JP130.1, U34.13
D146: JP130.2, U34.12
D147: JP130.8, U34.32
D148: JP130.7, U34.1
D149: JP130.6, U34.2
D150: JP130.5, U34.9
D151: JP130.4, U34.10
D152: JP130.3, U34.11
D153: JP129.12, U34.14
D154: JP138.1, U36.13
D155: JP138.2, U36.12
D156: JP138.8, U36.32
D157: JP138.7, U36.1
D158: JP138.6, U36.2
D159: JP138.5, U36.9
D160: JP138.4, U36.10
D161: JP138.3, U36.11
D162: JP137.12, U36.14
D163: JP146.1, U38.13
D164: JP146.2, U38.12
D165: JP146.8, U38.32
D166: JP146.7, U38.1
D167: JP146.6, U38.2
D168: JP146.5, U38.9
D169: JP146.4, U38.10
D170: JP146.3, U38.11
D171: JP145.12, U38.14
D172: JP154.1, U40.13
D173: JP154.2, U40.12
D174: JP154.8, U40.32
D175: JP154.7, U40.1
D176: JP154.6, U40.2
D177: JP154.5, U40.9
D178: JP154.4, U40.10
D179: JP154.3, U40.11
D180: JP153.12, U40.14
D181: JP162.1, U42.13
D182: JP162.2, U42.12
D183: JP162.8, U42.32
D184: JP162.7, U42.1
D185: JP162.6, U42.2
D186: JP162.5, U42.9
D187: JP162.4, U42.10
D188: JP162.3, U42.11
D189: JP161.12, U42.14
D190: JP170.1, U44.13
D191: JP170.2, U44.12
D192: JP170.8, U44.32
D193: JP170.7, U44.1
D194: JP170.6, U44.2
D195: JP170.5, U44.9
D196: JP170.4, U44.10
D197: JP170.3, U44.11
D198: JP169.12, U44.14
D199: JP178.1, U46.13
D200: JP178.2, U46.12
D201: JP178.8, U46.32
D202: JP178.7, U46.1
D203: JP178.6, U46.2
D204: JP178.5, U46.9
D205: JP178.4, U46.10
D206: JP178.3, U46.11
D207: JP177.12, U46.14
D208: JP186.1, U48.13
D209: JP186.2, U48.12
D210: JP186.8, U48.32
D211: JP186.7, U48.1
D212: JP186.6, U48.2
D213: JP186.5, U48.9
D214: JP186.4, U48.10
D215: JP186.3, U48.11
D216: JP185.12, U48.14
D217: JP194.1, U50.13
D218: JP194.2, U50.12
D219: JP194.8, U50.32
D220: JP194.7, U50.1
D221: JP194.6, U50.2
D222: JP194.5, U50.9
D223: JP194.4, U50.10
D224: JP194.3, U50.11
D225: JP193.12, U50.14
D226: JP202.1, U52.13
D227: JP202.2, U52.12
D228: JP202.8, U52.32
D229: JP202.7, U52.1
D230: JP202.6, U52.2
D231: JP202.5, U52.9
D232: JP202.4, U52.10
D233: JP202.3, U52.11
D234: JP201.12, U52.14
D235: JP210.1, U54.13
D236: JP210.2, U54.12
D237: JP210.8, U54.32
D238: JP210.7, U54.1
D239: JP210.6, U54.2
D240: JP210.5, U54.9
D241: JP210.4, U54.10
D242: JP210.3, U54.11
D243: JP209.12, U54.14
D244: JP218.1, U56.13
D245: JP218.2, U56.12
D246: JP218.8, U56.32
D247: JP218.7, U56.1
D248: JP218.6, U56.2
D249: JP218.5, U56.9
D250: JP218.4, U56.10
D251: JP218.3, U56.11
D252: JP217.12, U56.14
D253: JP226.1, U58.13
D254: JP226.2, U58.12
D255: JP226.8, U58.32
D256: JP226.7, U58.1
D257: JP226.6, U58.2
D258: JP226.5, U58.9
D259: JP226.4, U58.10
D260: JP226.3, U58.11
D261: JP225.12, U58.14
D262: JP234.1, U60.13
D263: JP234.2, U60.12
D264: JP234.8, U60.32
D265: JP234.7, U60.1
D266: JP234.6, U60.2
D267: JP234.5, U60.9
D268: JP234.4, U60.10
D269: JP234.3, U60.11
D270: JP233.12, U60.14
D271: JP242.1, U62.13
D272: JP242.2, U62.12
D273: JP242.8, U62.32
D274: JP242.7, U62.1
D275: JP242.6, U62.2
D276: JP242.5, U62.9
D277: JP242.4, U62.10
D278: JP242.3, U62.11
D279: JP241.12, U62.14
D280: JP250.1, U64.13
D281: JP250.2, U64.12
D282: JP250.8, U64.32
D283: JP250.7, U64.1
D284: JP250.6, U64.2
D285: JP250.5, U64.9
D286: JP250.4, U64.10
D287: JP250.3, U64.11
D288: JP249.12, U64.14
D289: JP258.1, U66.13
D290: JP258.2, U66.12
D291: JP258.8, U66.32
D292: JP258.7, U66.1
D293: JP258.6, U66.2
D294: JP258.5, U66.9
D295: JP258.4, U66.10
D296: JP258.3, U66.11
D297: JP257.12, U66.14
D298: JP266.1, U68.13
D299: JP266.2, U68.12
D300: JP266.8, U68.32
D301: JP266.7, U68.1
D302: JP266.6, U68.2
D303: JP266.5, U68.9
D304: JP266.4, U68.10
D305: JP266.3, U68.11
D306: JP265.12, U68.14
D307: JP274.1, U70.13
D308: JP274.2, U70.12
D309: JP274.8, U70.32
D310: JP274.7, U70.1
D311: JP274.6, U70.2
D312: JP274.5, U70.9
D313: JP274.4, U70.10
D314: JP274.3, U70.11
D315: JP273.12, U70.14
D316: JP282.1, U72.13
D317: JP282.2, U72.12
D318: JP282.8, U72.32
D319: JP282.7, U72.1
D320: JP282.6, U72.2
D321: JP282.5, U72.9
D322: JP282.4, U72.10
D323: JP282.3, U72.11
D324: JP281.12, U72.14
D325: JP290.1, U74.13
D326: JP290.2, U74.12
D327: JP290.8, U74.32
D328: JP290.7, U74.1
D329: JP290.6, U74.2
D330: JP290.5, U74.9
D331: JP290.4, U74.10
D332: JP290.3, U74.11
D333: JP289.12, U74.14
D334: JP298.1, U76.13
D335: JP298.2, U76.12
D336: JP298.8, U76.32
D337: JP298.7, U76.1
D338: JP298.6, U76.2
D339: JP298.5, U76.9
D340: JP298.4, U76.10
D341: JP298.3, U76.11
D342: JP297.12, U76.14
D343: JP306.1, U78.13
D344: JP306.2, U78.12
D345: JP306.8, U78.32
D346: JP306.7, U78.1
D347: JP306.6, U78.2
D348: JP306.5, U78.9
D349: JP306.4, U78.10
D350: JP306.3, U78.11
D351: JP305.12, U78.14
D352: JP314.1, U80.13
D353: JP314.2, U80.12
D354: JP314.8, U80.32
D355: JP314.7, U80.1
D356: JP314.6, U80.2
D357: JP314.5, U80.9
D358: JP314.4, U80.10
D359: JP314.3, U80.11
D360: JP313.12, U80.14
D361: JP322.1, U82.13
D362: JP322.2, U82.12
D363: JP322.8, U82.32
D364: JP322.7, U82.1
D365: JP322.6, U82.2
D366: JP322.5, U82.9
D367: JP322.4, U82.10
D368: JP322.3, U82.11
D369: JP321.12, U82.14
D370: JP330.1, U84.13
D371: JP330.2, U84.12
D372: JP330.8, U84.32
D373: JP330.7, U84.1
D374: JP330.6, U84.2
D375: JP330.5, U84.9
D376: JP330.4, U84.10
D377: JP330.3, U84.11
D378: JP329.12, U84.14
D379: JP338.1, U86.13
D380: JP338.2, U86.12
D381: JP338.8, U86.32
D382: JP338.7, U86.1
D383: JP338.6, U86.2
D384: JP338.5, U86.9
D385: JP338.4, U86.10
D386: JP338.3, U86.11
D387: JP337.12, U86.14
D388: JP346.1, U88.13
D389: JP346.2, U88.12
D390: JP346.8, U88.32
D391: JP346.7, U88.1
D392: JP346.6, U88.2
D393: JP346.5, U88.9
D394: JP346.4, U88.10
D395: JP346.3, U88.11
D396: JP345.12, U88.14
D397: JP354.1, U90.13
D398: JP354.2, U90.12
D399: JP354.8, U90.32
D400: JP354.7, U90.1
D401: JP354.6, U90.2
D402: JP354.5, U90.9
D403: JP354.4, U90.10
D404: JP354.3, U90.11
D405: JP353.12, U90.14
D406: JP362.1, U92.13
D407: JP362.2, U92.12
D408: JP362.8, U92.32
D409: JP362.7, U92.1
D410: JP362.6, U92.2
D411: JP362.5, U92.9
D412: JP362.4, U92.10
D413: JP362.3, U92.11
D414: JP361.12, U92.14
D415: JP370.1, U94.13
D416: JP370.2, U94.12
D417: JP370.8, U94.32
D418: JP370.7, U94.1
D419: JP370.6, U94.2
D420: JP370.5, U94.9
D421: JP370.4, U94.10
D422: JP370.3, U94.11
D423: JP369.12, U94.14
D424: JP378.1, U96.13
D425: JP378.2, U96.12
D426: JP378.8, U96.32
D427: JP378.7, U96.1
D428: JP378.6, U96.2
D429: JP378.5, U96.9
D430: JP378.4, U96.10
D431: JP378.3, U96.11
D432: JP377.12, U96.14
D433: JP386.1, U98.13
D434: JP386.2, U98.12
D435: JP386.8, U98.32
D436: JP386.7, U98.1
D437: JP386.6, U98.2
D438: JP386.5, U98.9
D439: JP386.4, U98.10
D440: JP386.3, U98.11
D441: JP385.12, U98.14
D442: JP394.1, U100.13
D443: JP394.2, U100.12
D444: JP394.8, U100.32
D445: JP394.7, U100.1
D446: JP394.6, U100.2
D447: JP394.5, U100.9
D448: JP394.4, U100.10
D449: JP394.3, U100.11
D450: JP393.12, U100.14
D451: JP402.1, U102.13
D452: JP402.2, U102.12
D453: JP402.8, U102.32
D454: JP402.7, U102.1
D455: JP402.6, U102.2
D456: JP402.5, U102.9
D457: JP402.4, U102.10
D458: JP402.3, U102.11
D459: JP401.12, U102.14
D460: JP410.1, U104.13
D461: JP410.2, U104.12
D462: JP410.8, U104.32
D463: JP410.7, U104.1
D464: JP410.6, U104.2
D465: JP410.5, U104.9
D466: JP410.4, U104.10
D467: JP410.3, U104.11
D468: JP409.12, U104.14
D469: JP418.1, U106.13
D470: JP418.2, U106.12
D471: JP418.8, U106.32
D472: JP418.7, U106.1
D473: JP418.6, U106.2
D474: JP418.5, U106.9
D475: JP418.4, U106.10
D476: JP418.3, U106.11
D477: JP417.12, U106.14
D478: JP426.1, U108.13
D479: JP426.2, U108.12
D480: JP426.8, U108.32
D481: JP426.7, U108.1
D482: JP426.6, U108.2
D483: JP426.5, U108.9
D484: JP426.4, U108.10
D485: JP426.3, U108.11
D486: JP425.12, U108.14
D487: JP434.1, U110.13
D488: JP434.2, U110.12
D489: JP434.8, U110.32
D490: JP434.7, U110.1
D491: JP434.6, U110.2
D492: JP434.5, U110.9
D493: JP434.4, U110.10
D494: JP434.3, U110.11
D495: JP433.12, U110.14
D496: JP442.1, U112.13
D497: JP442.2, U112.12
D498: JP442.8, U112.32
D499: JP442.7, U112.1
D500: JP442.6, U112.2
D501: JP442.5, U112.9
D502: JP442.4, U112.10
D503: JP442.3, U112.11
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
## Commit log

2013-11-01 Removing 3.3V firmware, updating README
2013-11-01 Fixing file name for Eagle files
2013-11-04 Updating Silk
2013-11-06 Giant Panel Created
2013-12-11 Update README.md
    Adding link to newspost on SFE homepage.
